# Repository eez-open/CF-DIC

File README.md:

Current-fed dual inductor converter (CF-DIC) project files

Inspired by article Filho, Barbi (1996), *[A comparison between two current-fed push-pull DC-DC converters-analysis, design and experimentation](https://www.researchgate.net/publication/3673781_A_comparison_between_two_current-fed_push-pull_DC-DC_converters-analysis_design_and_experimentation)* and made with great assistance of Dragoljub Aleksijević (aka *Macola*).

### Feature list

* Wide range input: 85 – 265 Vac, 120 – 380 Vdc
* Wide range output: 2.5 – 52.5 Vdc 
* Max. current 3 A continuously, or 5 A with forced-air cooling (max. power up to ~260 W)
* Output voltage controlled by tracker circuit or optionally with multiturn trimpot if fixed output voltage is required
* Cascaded PWM Controller LM5041B (sync buck + push-pull stage)
* Isolated HV power ground and signal ground for improved noise immunity
* HV buck section with high performance SiC MOSFET switches
* High performance Vitroperm 500F core material for power transformer
* Synchronous rectifier with low R(ds,on) MOSFET switches
* Over-voltage (OVP), short circuit protection and over-temperature protection (OTP) with latched shutdown and opto-isolated open-collector "Fault" output
* Over-current protection (OCP)
* QR flyback as bias power supply (VIPer35)
* Four bias power supply outputs: +6.5 V, -8 V and "floating" +12 V / -12 V that can be further regulated with LDOs
* Compact size: 157 x 92 x 45 mm
* Weight (with enclosure): 0.49 kg

### r5B6 prototype

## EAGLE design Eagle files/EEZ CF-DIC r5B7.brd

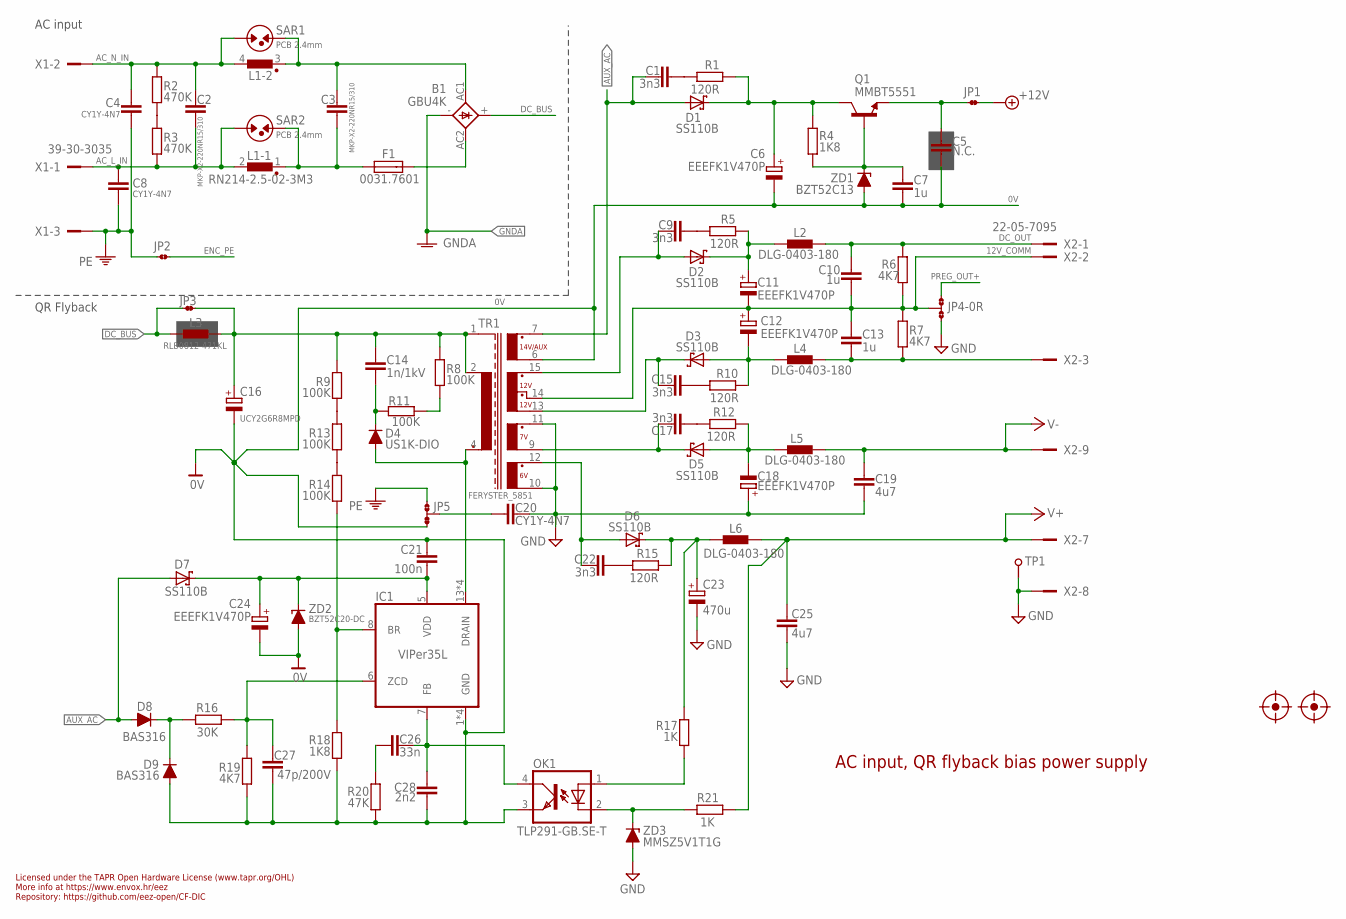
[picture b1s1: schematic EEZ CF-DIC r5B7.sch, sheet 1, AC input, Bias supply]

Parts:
B1: GBU4K; GBU4K_CRE
C1, C9, C15, C17, C22: 3n3; C0805
C2, C3: MKP-X2-220NR15/310; C150-072X183
C4, C8, C20: CY1Y-4N7; CY075-032X103
C5: N.C.; C0603
C6, C11, C12, C18, C24: EEEFK1V470P; CAPAE660X610N
C7, C10, C13: 1u; C0805
C14: 1n/1kV; C1210
C16: UCY2G6R8MPD; ECAP5/10.5
C19, C25: 4u7; C1206
C21: 100n; C0603
C23: 470u; ECAP5/10.5
C26: 33n; C0805
C27: 47p/200V; C0805
C28: 2n2; C0805
D1, D2, D3, D5, D6: SS110B; SMB
D4: US1K-DIO; DO214AA
D7: SS110B; SMA
D8, D9: BAS316; SOD323-R
F1: 0031.7601; FUSE_TR5
FM1, FM2: FIDUCIAL_2; FIDUCIAL_DUAL
IC1: VIPer35L; SOIC-16
JP1, JP3: JP2-NOCUT
JP2: JP2-CUT
JP4: 0R-JUMPA; A0R-JMP
JP5: JP3-CUT
L1: RN214-2.5-02-3M3; RN214; FARNELL 1191518
L2, L4, L5, L6: DLG-0403-180; DE0403
L3: RLB0812-471KL; FERSYTER_DSZ6
OK1: TLP291-GB.SE-T; SO4
Q1: MMBT5551; SOT23-BEC
R1, R5, R10, R12, R15: 120R; R0805
R2, R3: 470K; R1206
R4, R18: 1K8; R0805
R6, R7, R19: 4K7; R0805
R8, R9, R11, R13, R14: 100K; R1206
R16: 30K; R0805
R17, R21: 1K; R0805
R20: 47K; R0805
SAR1, SAR2: PCB 2.4mm; PCB-SAR_2.4MM
TP1: PCB_TEST_TABSHIELD; PCB_SHIELD_TAB
TR1: FERYSTER_5851; FERYSTER_5572
X1: 39-30-3035; MINIFIT_6659-3_CRE
X2: 22-05-7095; SPOX_22-05-7095
ZD1: BZT52C13; SOD123
ZD2: BZT52C20-DC; SOD123
ZD3: MMSZ5V1T1G; SOD123

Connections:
0V: C5.2, C6.2 (-), C7.2, C16.-, C21.1, C24.2 (-), C27.2, C28.2, D9.A, IC1.1 (GND), IC1.2 (GND), IC1.3 (GND), IC1.4 (GND), JP5.NC, OK1.3 (EMIT), R18.2, R19.1, R20.2, TR1.6 (S_AUX), ZD1.A, ZD2.A; also elsewhere on the board
6VAC: C22.2, D6.A, TR1.12 (6V_DOT)
7VAC: C17.2, D5.C, TR1.9 (7V)
12VAC1: C9.2, D2.A, TR1.15 (12V_DOT2)
12VAC2: C15.2, D3.C, TR1.13 (12V)
12V_COMM: C10.2, C11.2 (-), C12.1 (+), C13.1, JP4.2, R6.2, R7.1, TR1.14 (12V_DOT), X2.2
+6V_REC: C23.+, D6.C, L6.1, R15.1, R17.1
+12V: JP1.2; also elsewhere on the board
+12V_REC: C11.1 (+), D2.C, L2.1, R5.1
-7V_REC: C18.2 (-), D5.A, L5.1, R12.1
-12V: C13.2, L4.2, R7.2, X2.3
-12V_REC: C12.2 (-), D3.A, L4.1, R10.1
AC_L_IN: C2.2, C8.2, L1.2, R3.2, SAR2.1, X1.1
AC_N_IN: C2.1, C4.2, L1.4 (2), R2.1, SAR1.1, X1.2
AUX_AC: C1.2, D1.A, D7.A, D8.A, TR1.7 (S_AUX_DOT)
AUX_REC: C6.1 (+), D1.C, Q1.C, R1.1, R4.1
DC_BUS: B1.+, JP3.1, L3.P$1 (1); also elsewhere on the board
DC_OUT: C10.1, L2.2, R6.1, X2.1
ENC_PE: JP2.2
FB2: OK1.2 (C), R21.1, ZD3.C
GND: C18.1 (+), C19.1, C20.2, C23.-, C25.2, JP4.3, TP1.1, TR1.10 (6V), TR1.11 (7V_DOT), X2.8, ZD3.A; also elsewhere on the board
GNDA: B1.-; also elsewhere on the board
unnamed: C20.1, JP5.COM
unnamed: IC1.8 (BR), R14.2, R18.1
unnamed: C5.1, JP1.1, Q1.E
unnamed: C21.2, C24.1 (+), D7.C, IC1.5 (VDD), ZD2.C
unnamed: R2.2, R3.1
unnamed: B1.AC1, C3.1, L1.3 (1), SAR1.2
unnamed: C3.2, F1.1, L1.1, SAR2.2
unnamed: R13.2, R14.1
unnamed: R9.2, R13.1
unnamed: B1.AC2, F1.2
unnamed: C15.1, R10.2
unnamed: R8.2, R11.2
unnamed: C7.1, Q1.B, R4.2, ZD1.C
unnamed: OK1.1 (A), R17.2
unnamed: C14.2, D4.C, R11.1
unnamed: C26.2, C28.1, IC1.7 (FB), OK1.4 (COL)
unnamed: C9.1, R5.2
unnamed: C1.1, R1.2
unnamed: C27.1, IC1.6 (ZCD), R16.1, R19.2
unnamed: C17.1, R12.2
unnamed: C22.1, R15.2
unnamed: C26.1, R20.1
unnamed: D8.C, D9.C, R16.2
PE: C4.1, C8.1, JP2.1, JP5.NO, X1.3; also elsewhere on the board
PREG_OUT+: JP4.1; also elsewhere on the board
V+: C25.1, L6.2, R21.2, X2.7; also elsewhere on the board
V-: C19.2, L5.2, X2.9; also elsewhere on the board
VIPER+: C14.1, C16.+, JP3.2, L3.P$2 (2), R8.1, R9.1, TR1.1 (SHIELD), TR1.2
VIPER_D: D4.A, IC1.13 (DRAIN), IC1.14 (DRAIN), IC1.15 (DRAIN), IC1.16 (DRAIN), TR1.4 (P2_DOT)

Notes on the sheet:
Licensed under the TAPR Open Hardware License (www.tapr.org/OHL)
Repository: https://github.com/eez-open/CF-DIC
More info at https://www.envox.hr/eez
AC input, QR flyback bias power supply
QR Flyback
AC input

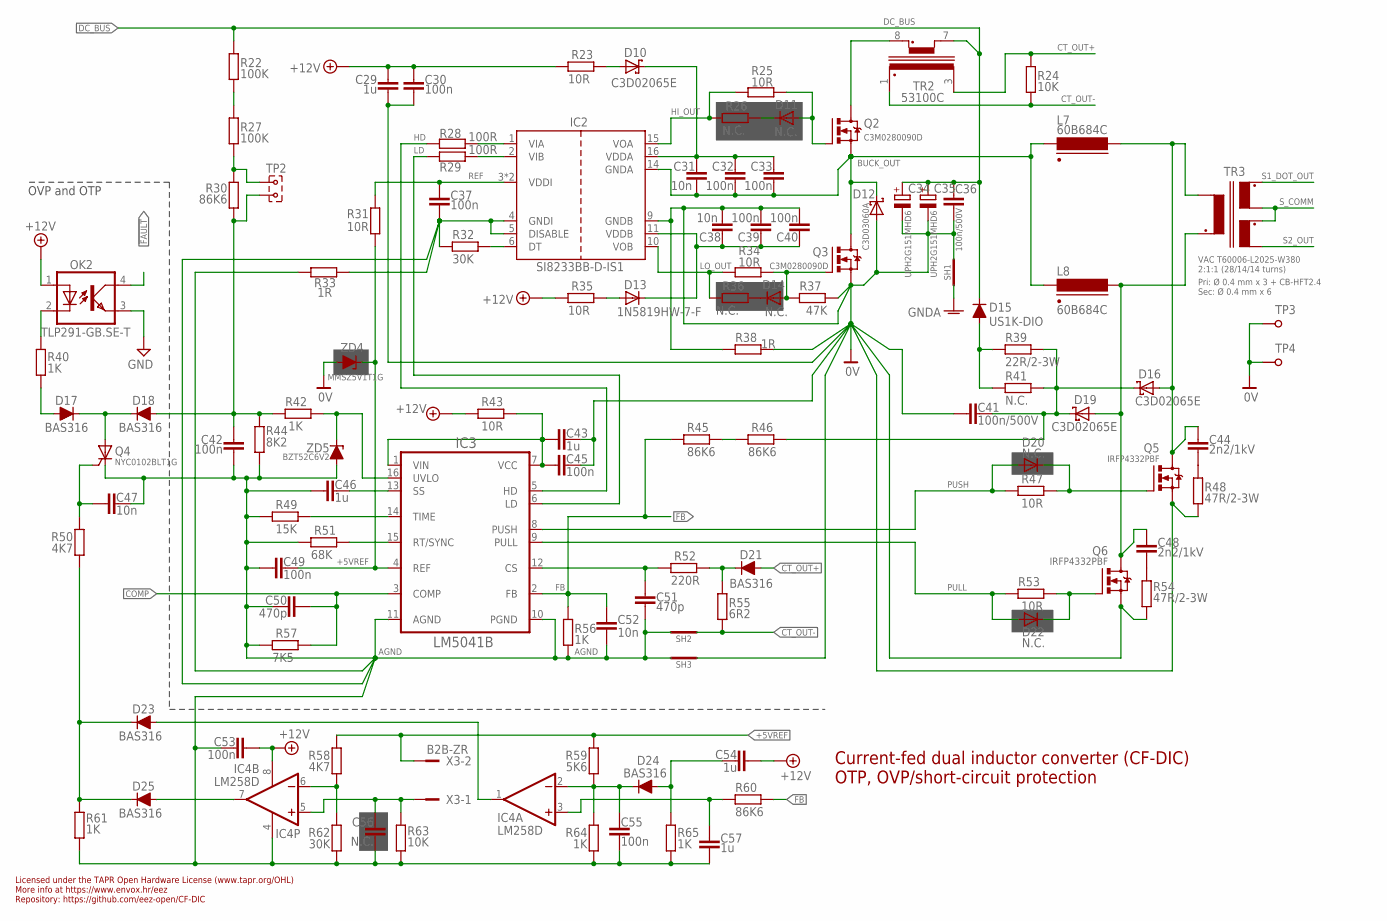
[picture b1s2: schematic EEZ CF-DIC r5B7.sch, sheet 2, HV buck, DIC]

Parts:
C29, C43, C46, C54, C57: 1u; C0805
C30, C32, C33, C37, C39, C40, C42, C45, C49, C53, C55: 100n; C0603
C31, C38, C47, C52: 10n; C0603
C34, C35: UPH2G151MHD6; ECAP7.5/18
C36, C41: 100n/500V; C1812
C44, C48: 2n2/1kV; C1210
C50, C51: 470p; C0805
C56: N.C.; C0603
D10, D16, D19: C3D02065E; TO252-L
D11, D14, D20, D22: N.C.; SOD323-W
D12: C3D03060A; TO220-2
D13: 1N5819HW-7-F; SOD323-W
D15: US1K-DIO; DO214AA
D17, D18, D21, D23, D24, D25: BAS316; SOD323-R
IC2: SI8233BB-D-IS1; SOIC-16
IC3: LM5041B; MTC16
IC4: LM258D; SOIC127P600X173-8N
L7, L8: 60B684C; MURATA_6000B
OK2: TLP291-GB.SE-T; SO4
Q2, Q3: C3M0280090D; TO247BV
Q4: NYC0102BLT1G; SOT23
Q5, Q6: IRFP4332PBF; TO247BV
R22, R27: 100K; R1206
R23, R25, R31, R34, R35, R43, R47, R53: 10R; R0805
R24, R63: 10K; R0805
R26, R36: N.C.; R0805
R28, R29: 100R; R0805
R30, R45, R46, R60: 86K6; R0805
R32, R62: 30K; R0805
R33, R38: 1R; R0805
R37: 47K; R0805
R39: 22R/2-3W; R2512
R40, R42, R56, R61, R64, R65: 1K; R0805
R41: N.C.; R2512
R44: 8K2; R0805
R48, R54: 47R/2-3W; R2512
R49: 15K; R0805
R50, R58: 4K7; R0805
R51: 68K; R0805
R52: 220R; R0805
R55: 6R2; R0805
R57: 7K5; R0805
R59: 5K6; R0805
SH1, SH2, SH3: SHORTNOHOLE; SHORT_NOHOLE
TP2: JUMPER-2PIN-2MM; 2MM-2
TP3, TP4: TEST-PIN1.2; TEST-PIN_1.2MM
TR2: 53100C; MURATA_5300
TR3: VAC T60006-L2025-W380; VAC_DUAL_SEC
X3: B2B-ZR
ZD4: MMSZ5V1T1G; SOD123
ZD5: BZT52C6V2; SOD123

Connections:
0V: C29.1, C30.1, C34.-, C35.-, C36.2, C38.2, C39.2, C40.2, C41.1, C43.2, C45.2, D12.2 (A), IC2.9 (GNDB), Q3.S, Q5.S, Q6.S, R37.2, R38.1, R38.2, R48.2, R54.2, SH1.P$2 (GND_B), SH3.P$1 (GND_A), TP3.1, TP4.1, ZD4.A; also elsewhere on the board
!FAULT: OK2.4 (COL); also elsewhere on the board
+5VREF: C49.2, IC3.4 (REF), R31.1, R58.2, R59.2, X3.2, ZD4.C
+12V: C29.2, C30.2, C53.1, C54.1, IC4.8 (V+), OK2.1 (A), R23.2, R35.2, R43.2; also elsewhere on the board
AGND: C37.1, C42.2, C46.1, C47.2, C49.1, C50.1, C51.1, C52.2, C53.2, C55.2, C56.1, C57.1, IC2.4 (GNDI), IC2.5 (DISABLE), IC3.10 (PGND), IC3.11 (AGND), IC4.4 (V-), Q4.1 (C), R32.1, R33.1, R33.2, R44.2, R49.2, R51.2, R56.2, R57.2, R61.2, R62.2, R63.2, R64.2, R65.2, SH2.P$2 (GND_B), SH3.P$2 (GND_B), ZD5.A; also elsewhere on the board
BUCK_OUT: C31.2, C32.2, C33.2, D12.1 (C), IC2.14 (GNDA), L7.2, L8.2, Q2.S, Q3.D
CLAMP_C: C41.2, D16.1 (C), D16.3 (C), D19.1 (C), D19.3 (C), R39.1, R41.1, R46.2
COMP: C50.2, IC3.3 (COMP), R57.1; also elsewhere on the board
CT_OUT+: D21.A, R24.1, TR2.3 (S)
CT_OUT-: R24.2, R55.2, SH2.P$1 (GND_A), TR2.1 (S_DOT)
DC_BUS: C34.+, C35.+, C36.1, D15.C, R22.1, TR2.7; also elsewhere on the board
FB: C52.1, IC3.2 (FB), R45.1, R56.1, R60.1
GND: OK2.3 (EMIT); also elsewhere on the board
GNDA: SH1.P$1 (GND_A); also elsewhere on the board
HD: IC3.5 (HD), R28.2
HI_OUT: IC2.15 (VOA), R25.2, R26.2
LD: IC3.6 (LD), R29.2
LO_OUT: IC2.10 (VOB), R34.1, R36.1
L_PULL: C48.2, D19.2 (A), L8.1, Q6.D, TR3.P1_DOT (P_DOT)
L_PUSH: C44.2, D16.2 (A), L7.1, Q5.D, TR3.P1
unnamed: R27.2, R30.1, TP2.1
unnamed: C31.1, C32.1, C33.1, D10.1 (C), D10.3 (C), IC2.16 (VDDA)
unnamed: C48.1, R54.1
unnamed: R22.2, R27.1
unnamed: C55.1, D24.C, IC4.2 (-IN), R59.1, R64.1
unnamed: D20.C, Q5.G, R47.1
unnamed: D22.C, Q6.G, R53.1
unnamed: Q2.D, TR2.8 (P_DOT)
unnamed: IC3.15 (RT/SYNC), R51.1
unnamed: D11.A, Q2.G, R25.1
unnamed: IC3.14 (TIME), R49.1
unnamed: C46.2, IC3.13 (SS)
unnamed: IC3.16 (UVLO), R42.1, ZD5.C
unnamed: IC4.6 (-IN), R58.1, R62.1
unnamed: D14.A, Q3.G, R34.2, R37.1
unnamed: R45.2, R46.1
unnamed: D10.2 (A), R23.1
unnamed: OK2.2 (C), R40.1
unnamed: C57.2, IC4.3 (+IN), R60.2
unnamed: D15.A, R39.2, R41.2
unnamed: IC2.1 (VIA), R28.1
unnamed: C51.2, IC3.12 (CS), R52.2
unnamed: D23.A, IC4.1 (OUT)
unnamed: IC2.2 (VIB), R29.1
unnamed: C56.2, IC4.5 (+IN), R63.1, X3.1
unnamed: D11.C, R26.1
unnamed: D25.A, IC4.7 (OUT)
unnamed: IC2.6 (DT), R32.2
unnamed: D23.C, D25.C, R50.2, R61.1
unnamed: D14.C, R36.2
unnamed: C43.1, C45.1, IC3.1 (VIN), IC3.7 (VCC), R43.1
unnamed: C38.1, C39.1, C40.1, D13.C, IC2.11 (VDDB)
unnamed: D21.C, R52.1, R55.1
unnamed: C54.2, D24.A, R65.1
unnamed: D13.A, R35.1
unnamed: C44.1, R48.1
unnamed: C47.1, Q4.2 (G), R50.1
unnamed: D17.C, D18.C, Q4.3 (A)
unnamed: D17.A, R40.2
PULL: D22.A, IC3.9 (PULL), R53.2
PUSH: D20.A, IC3.8 (PUSH), R47.2
REF: C37.2, IC2.3 (VDDI), IC2.8 (VDDI), R31.2
S1_DOT_OUT: TR3.S1_DOT; also elsewhere on the board
S2_OUT: TR3.S2; also elsewhere on the board
S_COMM: TR3.S1, TR3.S2_DOT; also elsewhere on the board
UVLO: C42.1, D18.A, R30.2, R42.2, R44.1, TP2.2

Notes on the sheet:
Licensed under the TAPR Open Hardware License (www.tapr.org/OHL)
Repository: https://github.com/eez-open/CF-DIC
More info at https://www.envox.hr/eez
Current-fed dual inductor converter (CF-DIC) OTP, OVP/short-circuit protection
OVP and OTP
2:1:1 (28/14/14 turns)
Pri: Ø 0.4 mm x 3 + CB-HFT2.4
Sec: Ø 0.4 mm x 6

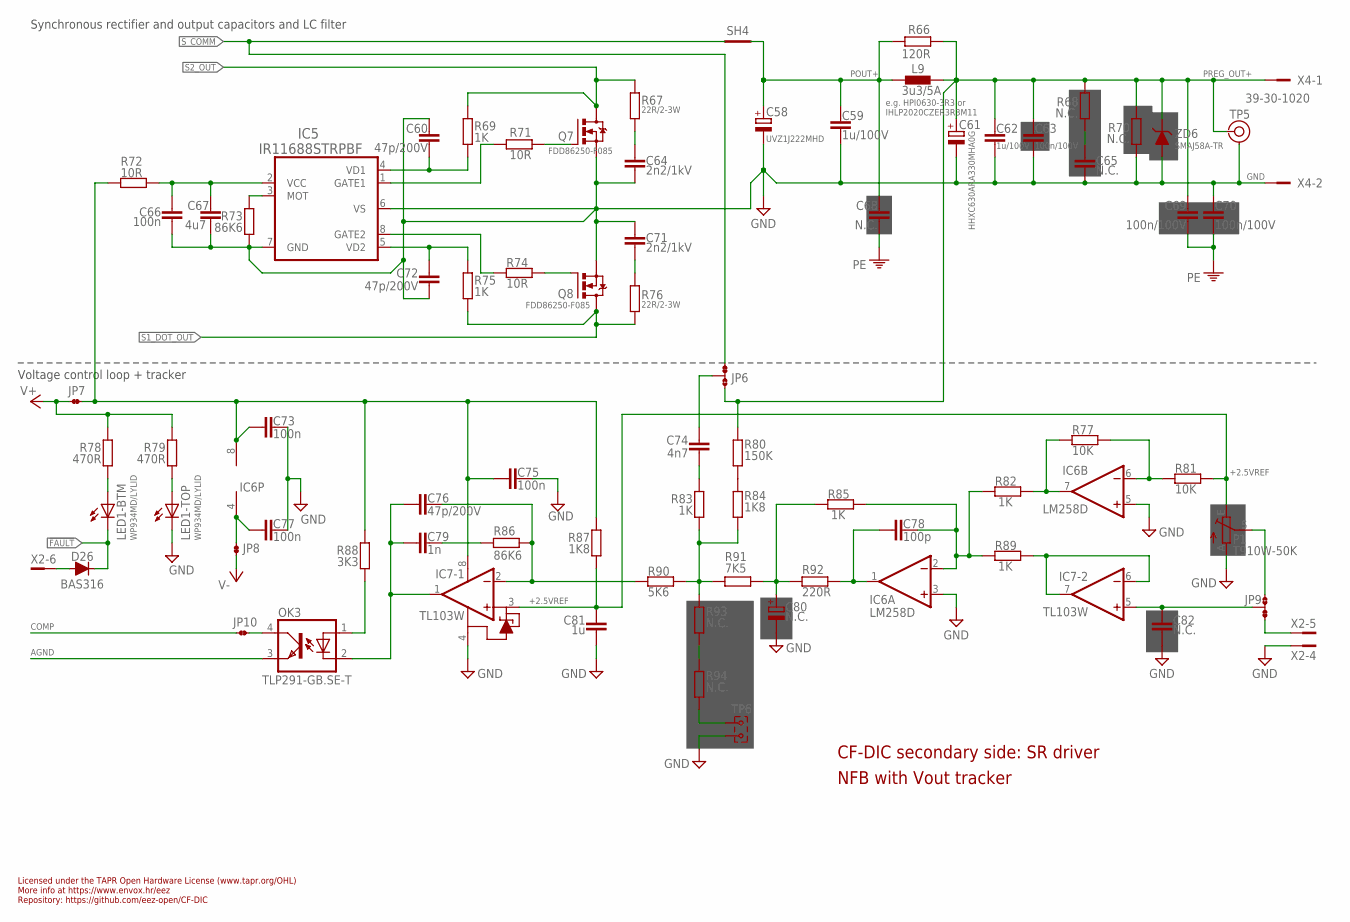
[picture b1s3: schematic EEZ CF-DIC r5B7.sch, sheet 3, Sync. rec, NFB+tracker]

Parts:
C58: UVZ1J222MHD; ECAP7.5/18-H35.5A
C59, C62: 1u/100V; C1206
C60, C72, C76: 47p/200V; C0805
C61: HHXC630ARA330MHA0G; CAPAE830X1050N
C63, C69, C70: 100n/100V; C1206
C64, C71: 2n2/1kV; C1210
C65, C68: N.C.; C1206
C66, C73, C75, C77: 100n; C0603
C67: 4u7; C1206
C74: 4n7; C0805
C78: 100p; C0805
C79: 1n; C0805
C80: N.C.; EC1206
C81: 1u; C0805
C82: N.C.; C0805
D26: BAS316; SOD323-R
IC5: IR11688STRPBF; SO8
IC6: LM258D; SOIC127P600X173-8N
IC7: TL103W; SOIC127P600X173-8N
JP6, JP9: JP3-CUT
JP7, JP8, JP10: JP2-NOCUT
L9: 3u3/5A; COILCRAFT_HPI0630
LED1: WP934MD/LYLID; WP934MD
OK3: TLP291-GB.SE-T; SO4
P1: T910W-50K; S64W
Q7, Q8: FDD86250-F085; TO229P990X239-3N
R66: 120R; R0805
R67, R76: 22R/2-3W; R2512
R68: N.C.; R1210
R69, R75, R82, R83, R85, R89: 1K; R0805
R70: N.C.; R2512
R71, R72, R74: 10R; R0805
R73, R86: 86K6; R0805
R77, R81: 10K; R0805
R78, R79: 470R; R0805
R80: 150K; R0805
R84, R87: 1K8; R0805
R88: 3K3; R0805
R90: 5K6; R0805
R91: 7K5; R0805
R92: 220R; R0805
R93, R94: N.C.; R0805
SH4: SHORTNOHOLE; SHORT_NOHOLE
TP5: TEST_POINT-2; TP_1.1MM_2
TP6: JUMPER-2PIN-2MM; 2MM-2
X2: 22-05-7095; SPOX_22-05-7095
X4: 39-30-1020; MINIFIT_39301020
ZD6: SMAJ58A-TR; DO214AC

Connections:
!FAULT: D26.C, LED1.BC (C); also elsewhere on the board
+2.5VREF: C81.1, IC7.3 (+IN1), P1.E, R81.2, R87.1
AGND: OK3.3 (EMIT); also elsewhere on the board
COMP: JP10.1; also elsewhere on the board
G1_OUT: Q7.1 (G), R71.1
G2_OUT: Q8.1 (G), R74.1
GATE1: IC5.1 (GATE1), R71.2
GATE2: IC5.8 (GATE2), R74.2
GND: C58.-, C59.2, C60.1, C61.-, C62.2, C63.2, C64.2, C65.1, C66.2, C67.2, C70.1, C71.2, C72.1, C73.2, C75.2, C77.2, C80.-, C81.2, C82.2, IC5.6 (VS), IC5.7 (GND), IC6.3 (+IN), IC6.5 (+IN), IC7.4 (VCC-), LED1.TC (C), P1.A, Q7.3 (S), Q8.3 (S), R70.1, R73.2, TP5.GND, TP6.2, X2.4, X4.2, ZD6.A; also elsewhere on the board
unnamed: D26.A, X2.6
unnamed: C65.2, R68.1
unnamed: C79.2, R86.2
unnamed: C76.2, IC7.2 (-IN1), R86.1, R90.1
unnamed: LED1.TA (A), R79.2
unnamed: R80.1, R84.2
unnamed: LED1.BA (A), R78.2
unnamed: IC5.3 (MOT), R73.1
unnamed: C74.2, R83.2
unnamed: C77.1, IC6.4 (V-), JP8.1
unnamed: JP10.2, OK3.4 (COL)
unnamed: C73.1, C75.1, IC6.8 (V+), IC7.8 (VCC+), JP7.2, R72.1, R87.2, R88.2
unnamed: R83.1, R84.1, R90.2, R91.2, R93.2
unnamed: IC6.7 (OUT), R77.1, R82.2
unnamed: C82.1, IC7.5 (+IN), JP9.COM
unnamed: JP9.NO, P1.S
unnamed: C78.2, IC6.2 (-IN), R82.1, R85.2, R89.1
unnamed: C71.1, R76.2
unnamed: C64.1, R67.2
unnamed: C74.1, JP6.COM
unnamed: R93.1, R94.2
unnamed: C76.1, C79.1, IC7.1 (OUT1), OK3.2 (C)
unnamed: R94.1, TP6.1
unnamed: IC6.6 (-IN), R77.2, R81.1
unnamed: C78.1, IC6.1 (OUT), R92.2
NFB_OFFSET: C80.+, R85.1, R91.1, R92.1
OK_A: OK3.1 (A), R88.1
PE: C68.2, C69.2, C70.2; also elsewhere on the board
POUT+: C58.+, C59.1, C68.1, L9.1, R66.1, SH4.P$2 (GND_B)
PREG_OUT+: C61.+, C62.1, C63.1, C69.1, JP6.NO, L9.2, R66.2, R68.2, R70.2, R80.2, TP5.TIP, X4.1, ZD6.C; also elsewhere on the board
S1_DOT_OUT: Q8.2 (D), R75.1, R76.1; also elsewhere on the board
S2_OUT: Q7.2 (D), R67.1, R69.2; also elsewhere on the board
SYNC_VCC: C66.1, C67.1, IC5.2 (VCC), R72.2
S_COMM: JP6.NC, SH4.P$1 (GND_A); also elsewhere on the board
U_CTRL: JP9.NC, X2.5
U_MON1: IC7.6 (-IN), IC7.7 (OUT), R89.2
V+: JP7.1, R78.1, R79.1; also elsewhere on the board
V-: JP8.2; also elsewhere on the board
VD1: C60.2, IC5.4 (VD1), R69.1
VD2: C72.2, IC5.5 (VD2), R75.2

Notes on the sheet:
Licensed under the TAPR Open Hardware License (www.tapr.org/OHL)
Repository: https://github.com/eez-open/CF-DIC
More info at https://www.envox.hr/eez
CF-DIC secondary side: SR driver
NFB with Vout tracker
Voltage control loop + tracker
Synchronous rectifier and output capacitors and LC filter
e.g. HPI0630-3R3 or IHLP2020CZER3R3M11

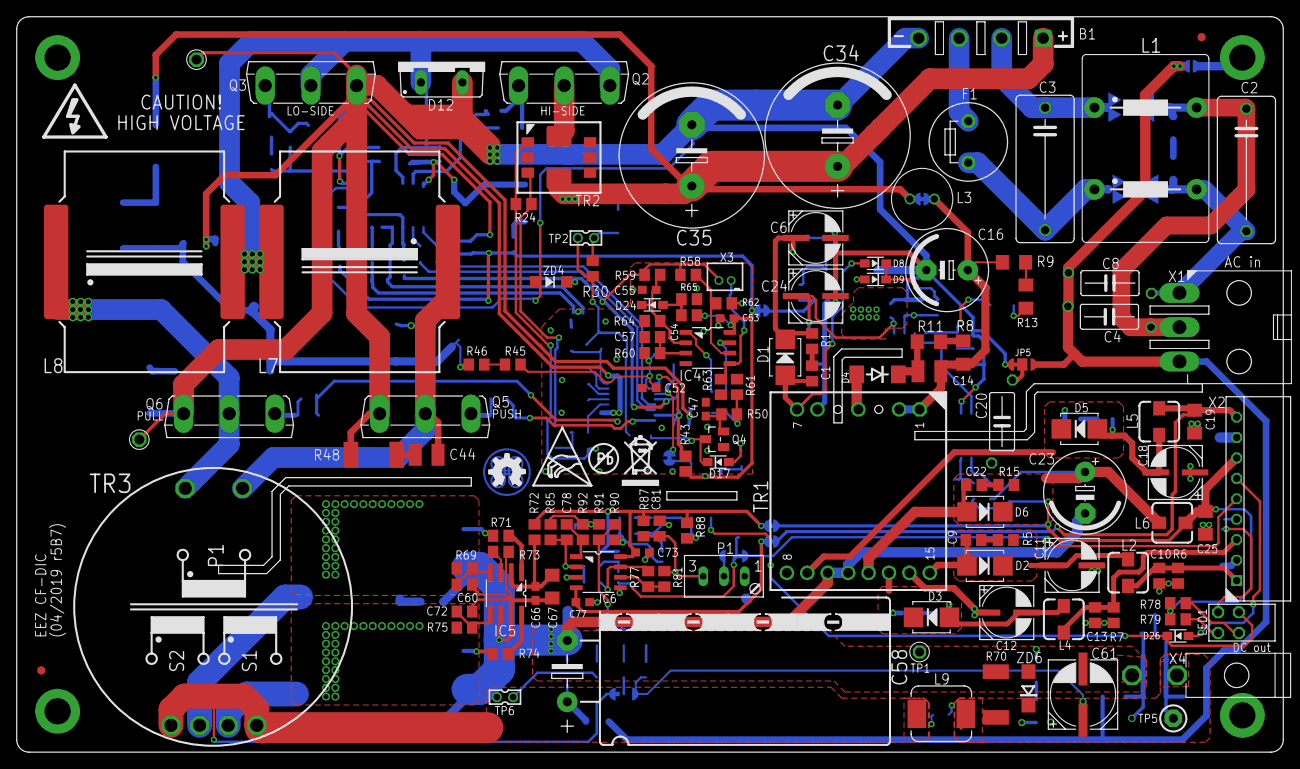
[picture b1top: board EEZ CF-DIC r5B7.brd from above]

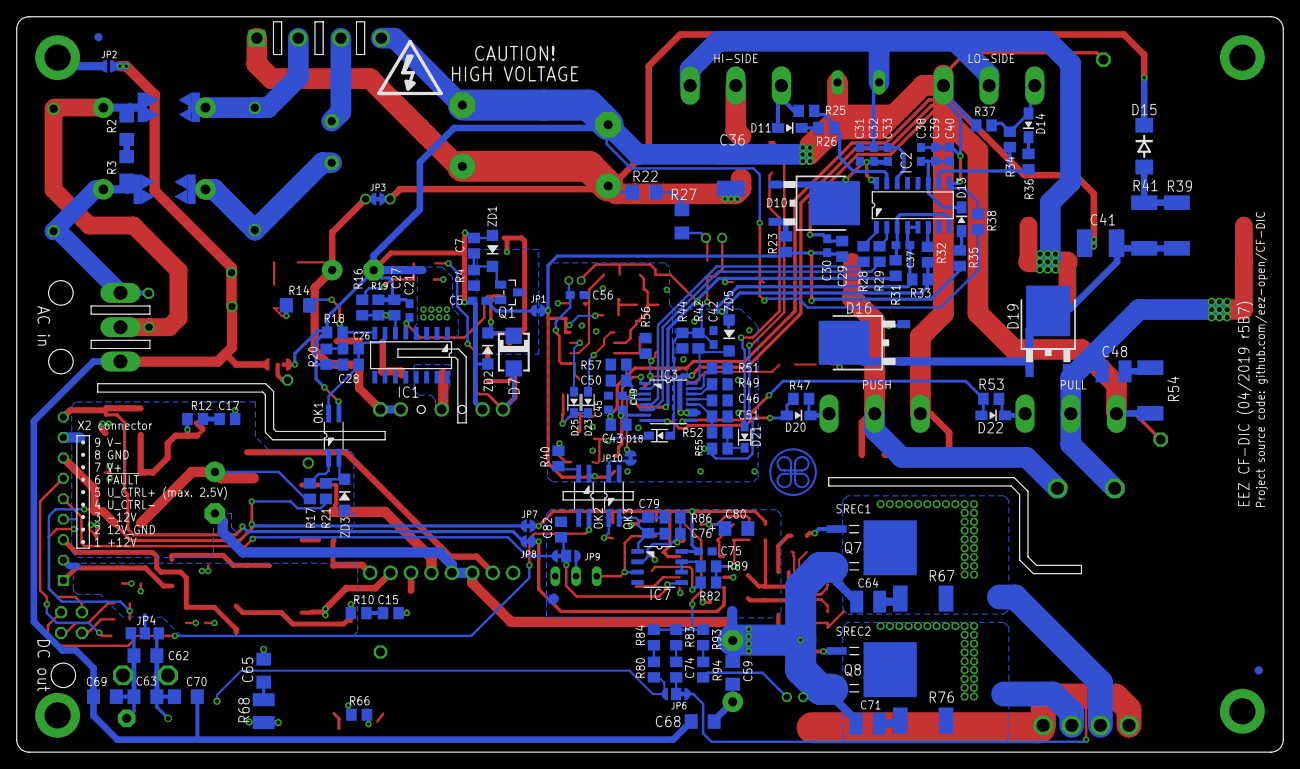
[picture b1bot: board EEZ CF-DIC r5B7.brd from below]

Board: 2 copper layers, 155.0 x 90.0 mm, 274 parts (136 on the bottom side), 149 nets.

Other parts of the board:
EEZ_SIGNATURE: SIGNATURESMALL; SIGNATURE_5MM
U$2: RECYCLE_BIN1/8
U$4: ESD_SYMBOL
U$7: PB_SMALL

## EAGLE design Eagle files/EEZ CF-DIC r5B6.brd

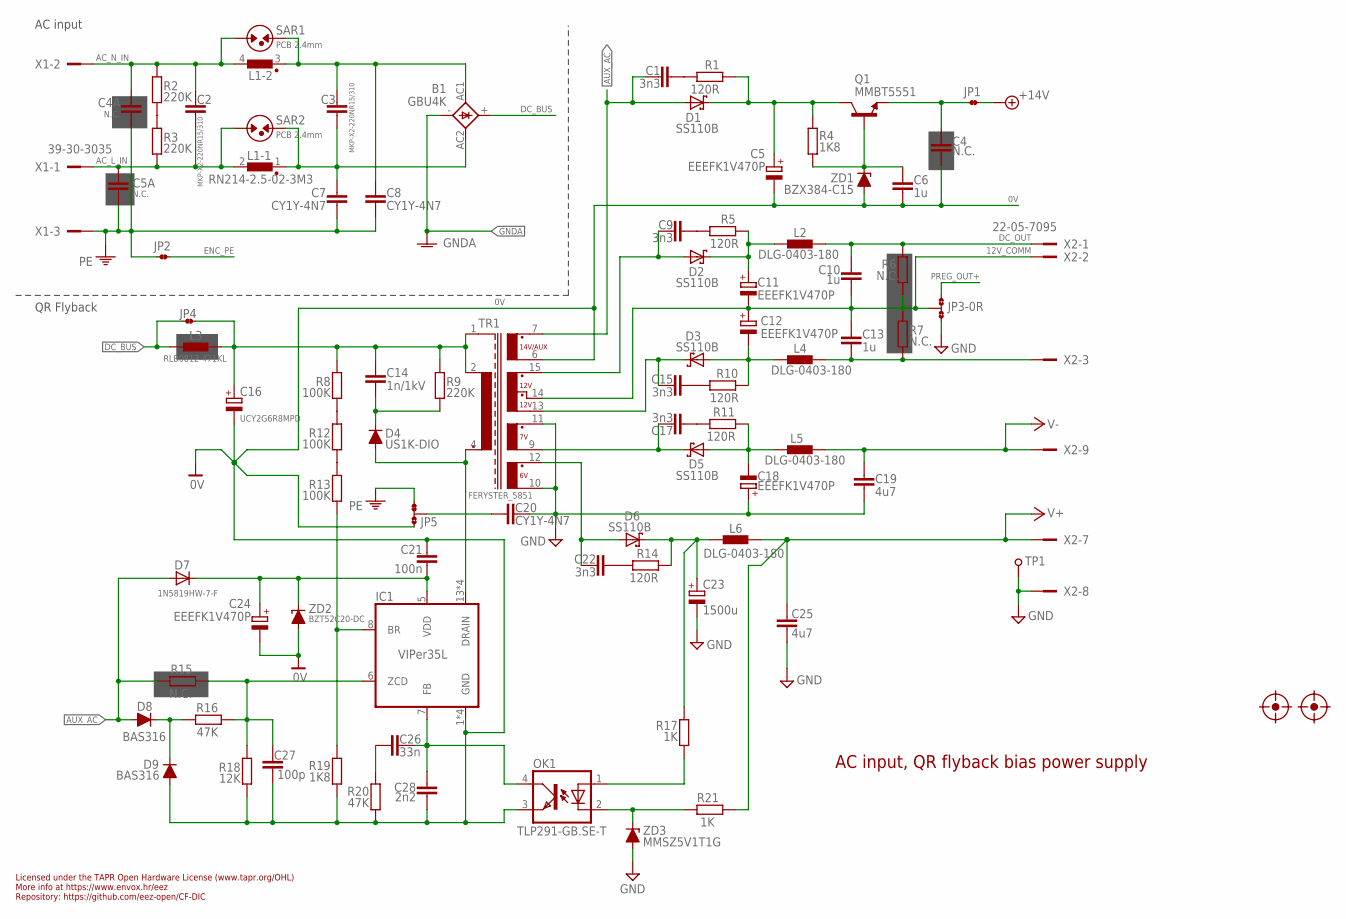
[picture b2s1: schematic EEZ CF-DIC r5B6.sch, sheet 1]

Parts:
B1: GBU4K; GBU4K_CRE
C1, C9, C15, C17, C22: 3n3; C0805
C2, C3: MKP-X2-220NR15/310; C150-072X183
C4: N.C.; C0603
C4A: N.C.; CY075-032X103-ROTATED
C5, C11, C12, C18, C24: EEEFK1V470P; CAPAE660X610N
C5A: N.C.; CY075-032X103
C6, C10, C13: 1u; C0805
C7, C8, C20: CY1Y-4N7; CY075-032X103
C14: 1n/1kV; C1210
C16: UCY2G6R8MPD; ECAP5/10.5
C19, C25: 4u7; C1206
C21: 100n; C0603
C23: 1500u; ECAP5/13
C26: 33n; C0805
C27: 100p; C0805
C28: 2n2; C0805
D1, D2, D3, D5, D6: SS110B; SMB
D4: US1K-DIO; DO214AA
D7: 1N5819HW-7-F; SOD323-W
D8, D9: BAS316; SOD323-R
FM1, FM2: FIDUCIAL_2; FIDUCIAL_DUAL
IC1: VIPer35L; SOIC-16
JP1, JP2, JP4: JP2-NOCUT
JP3: 0R-JUMPA; A0R-JMP
JP5: JP3-CUT
L1: RN214-2.5-02-3M3; RN214; FARNELL 1191518
L2, L4, L5, L6: DLG-0403-180; DE0403
L3: RLB0812-471KL; FERSYTER_DSZ6
OK1: TLP291-GB.SE-T; SO4
Q1: MMBT5551; SOT23-BEC
R1, R5, R10, R11, R14: 120R; R0805
R2, R3, R9: 220K; R1206
R4, R19: 1K8; R0805
R6, R7, R15: N.C.; R0805
R8, R12, R13: 100K; R1206
R16, R20: 47K; R0805
R17, R21: 1K; R0805
R18: 12K; R0805
SAR1, SAR2: PCB 2.4mm; PCB-SAR_2.4MM
TP1: PCB_TEST_TABSHIELD; PCB_SHIELD_TAB
TR1: FERYSTER_5851; FERYSTER_5572
X1: 39-30-3035; MINIFIT_6659-3_CRE
X2: 22-05-7095; SPOX_22-05-7095
ZD1: BZX384-C15; SOD323-W
ZD2: BZT52C20-DC; SOD123
ZD3: MMSZ5V1T1G; SOD323-W

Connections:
0V: C4.2, C5.2 (-), C6.2, C16.-, C21.1, C24.2 (-), C27.2, C28.2, D9.A, IC1.1 (GND), IC1.2 (GND), IC1.3 (GND), IC1.4 (GND), JP5.NO, OK1.3 (EMIT), R18.1, R19.2, R20.2, TR1.6 (S_AUX), ZD1.A, ZD2.A; also elsewhere on the board
6VAC: C22.2, D6.A, TR1.12 (6V_DOT)
7VAC: C17.2, D5.C, TR1.9 (7V)
12VAC1: C9.2, D2.A, TR1.15 (12V_DOT2)
12VAC2: C15.2, D3.C, TR1.13 (12V)
12V_COMM: C10.2, C11.2 (-), C12.1 (+), C13.1, JP3.2, R6.2, R7.1, TR1.14 (12V_DOT), X2.2
+6V_REC: C23.+, D6.C, L6.1, R14.1, R17.1
+12V_REC: C11.1 (+), D2.C, L2.1, R5.1
+14V: JP1.2; also elsewhere on the board
-7V_REC: C18.2 (-), D5.A, L5.1, R11.1
-12V: C13.2, L4.2, R7.2, X2.3
-12V_REC: C12.2 (-), D3.A, L4.1, R10.1
AC_L_IN: C2.2, C5A.2, L1.2, R3.2, SAR2.1, X1.1
AC_N_IN: C2.1, C4A.2, L1.4 (2), R2.1, SAR1.1, X1.2
AUX_AC: C1.2, D1.A, D7.A, D8.A, R15.2, TR1.7 (S_AUX_DOT)
AUX_REC: C5.1 (+), D1.C, Q1.C, R1.1, R4.1
DC_BUS: B1.+, JP4.1, L3.P$1 (1); also elsewhere on the board
DC_OUT: C10.1, L2.2, R6.1, X2.1
ENC_PE: JP2.2
FB2: OK1.2 (C), R21.1, ZD3.C
GND: C18.1 (+), C19.1, C20.2, C23.-, C25.2, JP3.3, TP1.1, TR1.10 (6V), TR1.11 (7V_DOT), X2.8, ZD3.A; also elsewhere on the board
GNDA: B1.-; also elsewhere on the board
unnamed: C20.1, JP5.COM
unnamed: IC1.8 (BR), R13.2, R19.1
unnamed: C4.1, JP1.1, Q1.E
unnamed: C21.2, C24.1 (+), D7.C, IC1.5 (VDD), ZD2.C
unnamed: R2.2, R3.1
unnamed: B1.AC1, C3.1, C8.2, L1.3 (1), SAR1.2
unnamed: B1.AC2, C3.2, C7.2, L1.1, SAR2.2
unnamed: R12.2, R13.1
unnamed: R8.2, R12.1
unnamed: C15.1, R10.2
unnamed: C6.1, Q1.B, R4.2, ZD1.C
unnamed: OK1.1 (A), R17.2
unnamed: C14.2, D4.C, R9.2
unnamed: C26.2, C28.1, IC1.7 (FB), OK1.4 (COL)
unnamed: C9.1, R5.2
unnamed: C1.1, R1.2
unnamed: C27.1, IC1.6 (ZCD), R15.1, R16.1, R18.2
unnamed: C17.1, R11.2
unnamed: C22.1, R14.2
unnamed: C26.1, R20.1
unnamed: D8.C, D9.C, R16.2
PE: C4A.1, C5A.1, C7.1, C8.1, JP2.1, JP5.NC, X1.3; also elsewhere on the board
PREG_OUT+: JP3.1; also elsewhere on the board
V+: C25.1, L6.2, R21.2, X2.7; also elsewhere on the board
V-: C19.2, L5.2, X2.9; also elsewhere on the board
VIPER+: C14.1, C16.+, JP4.2, L3.P$2 (2), R8.1, R9.1, TR1.1 (SHIELD), TR1.2
VIPER_D: D4.A, IC1.13 (DRAIN), IC1.14 (DRAIN), IC1.15 (DRAIN), IC1.16 (DRAIN), TR1.4 (P2_DOT)

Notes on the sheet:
Licensed under the TAPR Open Hardware License (www.tapr.org/OHL)
Repository: https://github.com/eez-open/CF-DIC
More info at https://www.envox.hr/eez
AC input, QR flyback bias power supply
QR Flyback
AC input

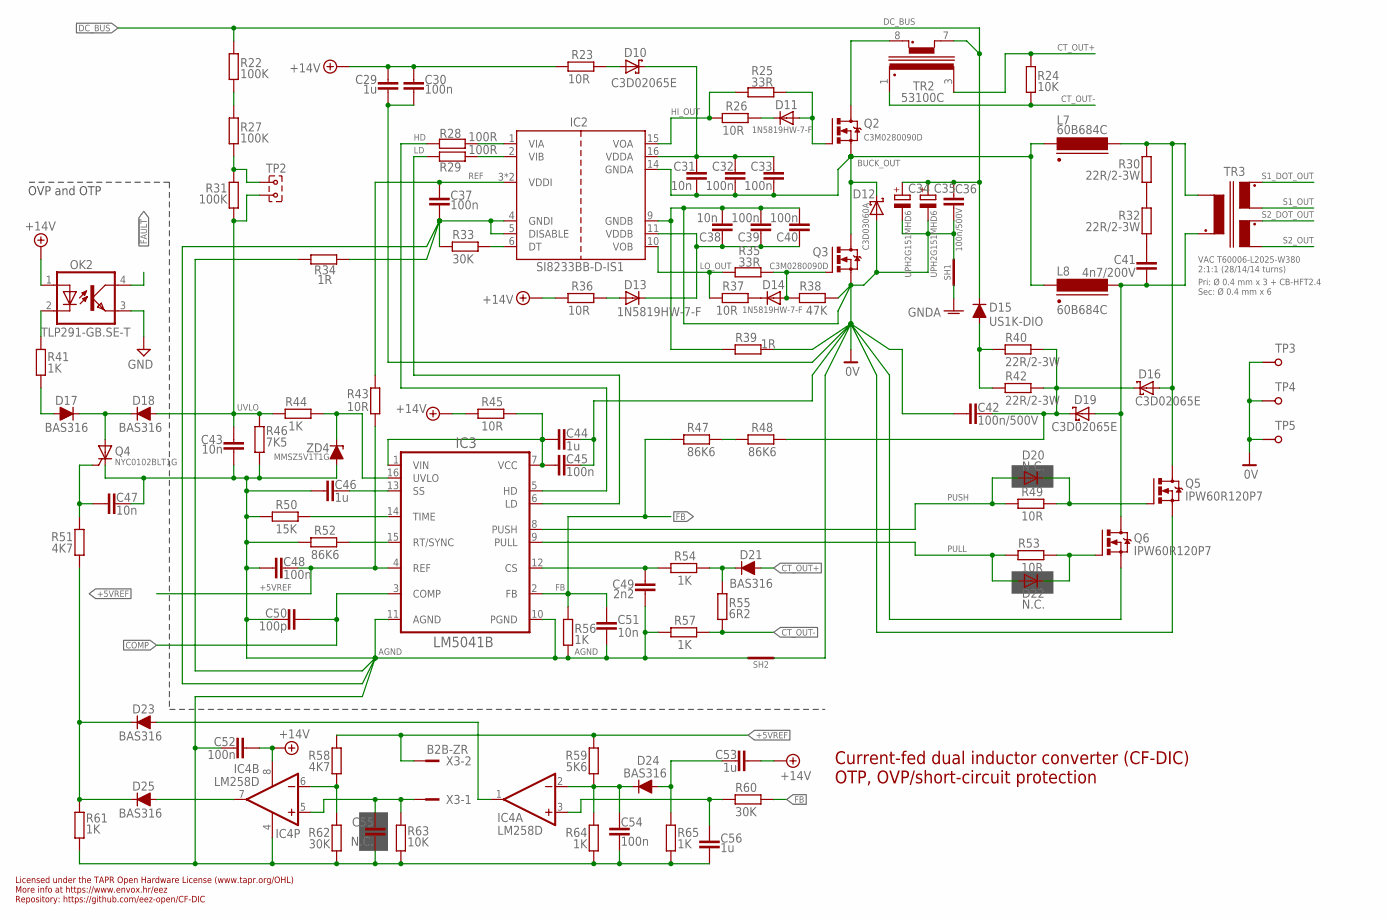
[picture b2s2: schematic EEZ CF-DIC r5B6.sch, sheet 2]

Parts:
C29, C44, C46, C53, C56: 1u; C0805
C30, C32, C33, C37, C39, C40, C45, C48, C52, C54: 100n; C0603
C31, C38, C43, C47, C51: 10n; C0603
C34, C35: UPH2G151MHD6; ECAP7.5/18
C36, C42: 100n/500V; C1812
C41: 4n7/200V; C1210
C49: 2n2; C0805
C50: 100p; C0805
C55: N.C.; C0603
D10, D16, D19: C3D02065E; TO252-L
D11, D13, D14: 1N5819HW-7-F; SOD323-W
D12: C3D03060A; TO220-2
D15: US1K-DIO; DO214AA
D17, D18, D21, D23, D24, D25: BAS316; SOD323-R
D20, D22: N.C.; SOD323-W
IC2: SI8233BB-D-IS1; SOIC-16
IC3: LM5041B; MTC16
IC4: LM258D; SOIC127P600X173-8N
L7, L8: 60B684C; MURATA_6000B
OK2: TLP291-GB.SE-T; SO4
Q2, Q3: C3M0280090D; TO247BV
Q4: NYC0102BLT1G; SOT23
Q5, Q6: IPW60R120P7; TO247BV
R22, R27, R31: 100K; R1206
R23, R26, R36, R37, R43, R45, R49, R53: 10R; R0805
R24, R63: 10K; R0805
R25, R35: 33R; R0805
R28, R29: 100R; R0805
R30, R32, R40, R42: 22R/2-3W; R2512
R33, R60, R62: 30K; R0805
R34, R39: 1R; R0805
R38: 47K; R0805
R41, R44, R54, R56, R57, R61, R64, R65: 1K; R0805
R46: 7K5; R0805
R47, R48, R52: 86K6; R0805
R50: 15K; R0805
R51, R58: 4K7; R0805
R55: 6R2; R0805
R59: 5K6; R0805
SH1, SH2: SHORTNOHOLE; SHORT_NOHOLE
TP2: JUMPER-2PIN-2MM; 2MM-2
TP3, TP4, TP5: TEST-PIN1.2; TEST-PIN_1.2MM
TR2: 53100C; MURATA_5300
TR3: VAC T60006-L2025-W380; VAC_DUAL_SEC
X3: B2B-ZR
ZD4: MMSZ5V1T1G; SOD323-W

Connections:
0V: C29.1, C30.1, C34.-, C35.-, C36.2, C38.2, C39.2, C40.2, C42.1, C44.2, C45.2, D12.2 (A), IC2.9 (GNDB), Q3.S, Q5.S, Q6.S, R38.2, R39.1, R39.2, SH1.P$2 (GND_B), SH2.P$1 (GND_A), TP3.1, TP4.1, TP5.1; also elsewhere on the board
!FAULT: OK2.4 (COL); also elsewhere on the board
+5VREF: C48.2, IC3.4 (REF), R43.1, R58.2, R59.2, X3.2; also elsewhere on the board
+14V: C29.2, C30.2, C52.1, C53.1, IC4.8 (V+), OK2.1 (A), R23.2, R36.2, R45.2; also elsewhere on the board
AGND: C37.1, C43.2, C46.1, C47.2, C48.1, C49.1, C50.1, C51.2, C52.2, C54.2, C55.1, C56.1, IC2.4 (GNDI), IC2.5 (DISABLE), IC3.10 (PGND), IC3.11 (AGND), IC4.4 (V-), Q4.1 (C), R33.1, R34.1, R34.2, R46.2, R50.2, R52.2, R56.2, R57.2, R61.2, R62.2, R63.2, R64.2, R65.2, SH2.P$2 (GND_B), ZD4.A; also elsewhere on the board
BUCK_OUT: C31.2, C32.2, C33.2, D12.1 (C), IC2.14 (GNDA), L7.2, L8.2, Q2.S, Q3.D
CLAMP_C: C42.2, D16.1 (C), D16.3 (C), D19.1 (C), D19.3 (C), R40.1, R42.1, R48.2
COMP: C50.2, IC3.3 (COMP); also elsewhere on the board
CT_OUT+: D21.A, R24.1, TR2.3 (S)
CT_OUT-: R24.2, R55.2, R57.1, TR2.1 (S_DOT)
DC_BUS: C34.+, C35.+, C36.1, D15.C, R22.1, TR2.7; also elsewhere on the board
FB: C51.1, IC3.2 (FB), R47.1, R56.1, R60.1
GND: OK2.3 (EMIT); also elsewhere on the board
GNDA: SH1.P$1 (GND_A); also elsewhere on the board
HD: IC3.5 (HD), R28.2
HI_OUT: IC2.15 (VOA), R25.2, R26.2
LD: IC3.6 (LD), R29.2
LO_OUT: IC2.10 (VOB), R35.1, R37.1
L_PULL: C41.2, D19.2 (A), L8.1, Q6.D, TR3.P1_DOT (P_DOT)
L_PUSH: D16.2 (A), L7.1, Q5.D, R30.2, TR3.P1
unnamed: R27.2, R31.1, TP2.1
unnamed: C31.1, C32.1, C33.1, D10.1 (C), D10.3 (C), IC2.16 (VDDA)
unnamed: R30.1, R32.2
unnamed: R22.2, R27.1
unnamed: C54.1, D24.C, IC4.2 (-IN), R59.1, R64.1
unnamed: D20.C, Q5.G, R49.1
unnamed: D22.C, Q6.G, R53.1
unnamed: Q2.D, TR2.8 (P_DOT)
unnamed: C41.1, R32.1
unnamed: IC3.15 (RT/SYNC), R52.1
unnamed: D11.A, Q2.G, R25.1
unnamed: IC3.14 (TIME), R50.1
unnamed: C46.2, IC3.13 (SS)
unnamed: IC3.16 (UVLO), R44.1, ZD4.C
unnamed: IC4.6 (-IN), R58.1, R62.1
unnamed: D14.A, Q3.G, R35.2, R38.1
unnamed: R47.2, R48.1
unnamed: D10.2 (A), R23.1
unnamed: OK2.2 (C), R41.1
unnamed: C56.2, IC4.3 (+IN), R60.2
unnamed: D15.A, R40.2, R42.2
unnamed: IC2.1 (VIA), R28.1
unnamed: C49.2, IC3.12 (CS), R54.2
unnamed: D23.A, IC4.1 (OUT)
unnamed: IC2.2 (VIB), R29.1
unnamed: C55.2, IC4.5 (+IN), R63.1, X3.1
unnamed: D11.C, R26.1
unnamed: D25.A, IC4.7 (OUT)
unnamed: IC2.6 (DT), R33.2
unnamed: D23.C, D25.C, R51.2, R61.1
unnamed: D14.C, R37.2
unnamed: C44.1, C45.1, IC3.1 (VIN), IC3.7 (VCC), R45.1
unnamed: C38.1, C39.1, C40.1, D13.C, IC2.11 (VDDB)
unnamed: D21.C, R54.1, R55.1
unnamed: C53.2, D24.A, R65.1
unnamed: D13.A, R36.1
unnamed: C47.1, Q4.2 (G), R51.1
unnamed: D17.C, D18.C, Q4.3 (A)
unnamed: D17.A, R41.2
PULL: D22.A, IC3.9 (PULL), R53.2
PUSH: D20.A, IC3.8 (PUSH), R49.2
REF: C37.2, IC2.3 (VDDI), IC2.8 (VDDI), R43.2
S1_DOT_OUT: TR3.S1_DOT; also elsewhere on the board
S1_OUT: TR3.S1; also elsewhere on the board
S2_DOT_OUT: TR3.S2_DOT; also elsewhere on the board
S2_OUT: TR3.S2; also elsewhere on the board
UVLO: C43.1, D18.A, R31.2, R44.2, R46.1, TP2.2; also elsewhere on the board

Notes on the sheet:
Licensed under the TAPR Open Hardware License (www.tapr.org/OHL)
Repository: https://github.com/eez-open/CF-DIC
More info at https://www.envox.hr/eez
Current-fed dual inductor converter (CF-DIC) OTP, OVP/short-circuit protection
OVP and OTP
2:1:1 (28/14/14 turns)
Pri: Ø 0.4 mm x 3 + CB-HFT2.4
Sec: Ø 0.4 mm x 6

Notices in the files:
parts and their libraries:
EEZ_inductors_and_transformers: This work is licensed under the TAPR Open Hardware License.
